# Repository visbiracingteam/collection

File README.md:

# collection
This is my latest git repository.
<br>
author-vishnu bijarniya

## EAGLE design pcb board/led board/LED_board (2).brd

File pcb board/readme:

I have designed boards related to the accumulator of a racing car. These boards need complete knowledge of eagle and PCB design related circuit analysis.
if you want to know about flex pcb and its application, I have done so in finding a solution for a flexible connection that we can add to the thermistor and cell module to connect with pcb board. It may be the solution to the split that we get during running of car.

link: https://drive.google.com/file/d/1qWOxBujmZSA4xRGkHqqwPAvdQpyxN6gt/view?usp=drive_link

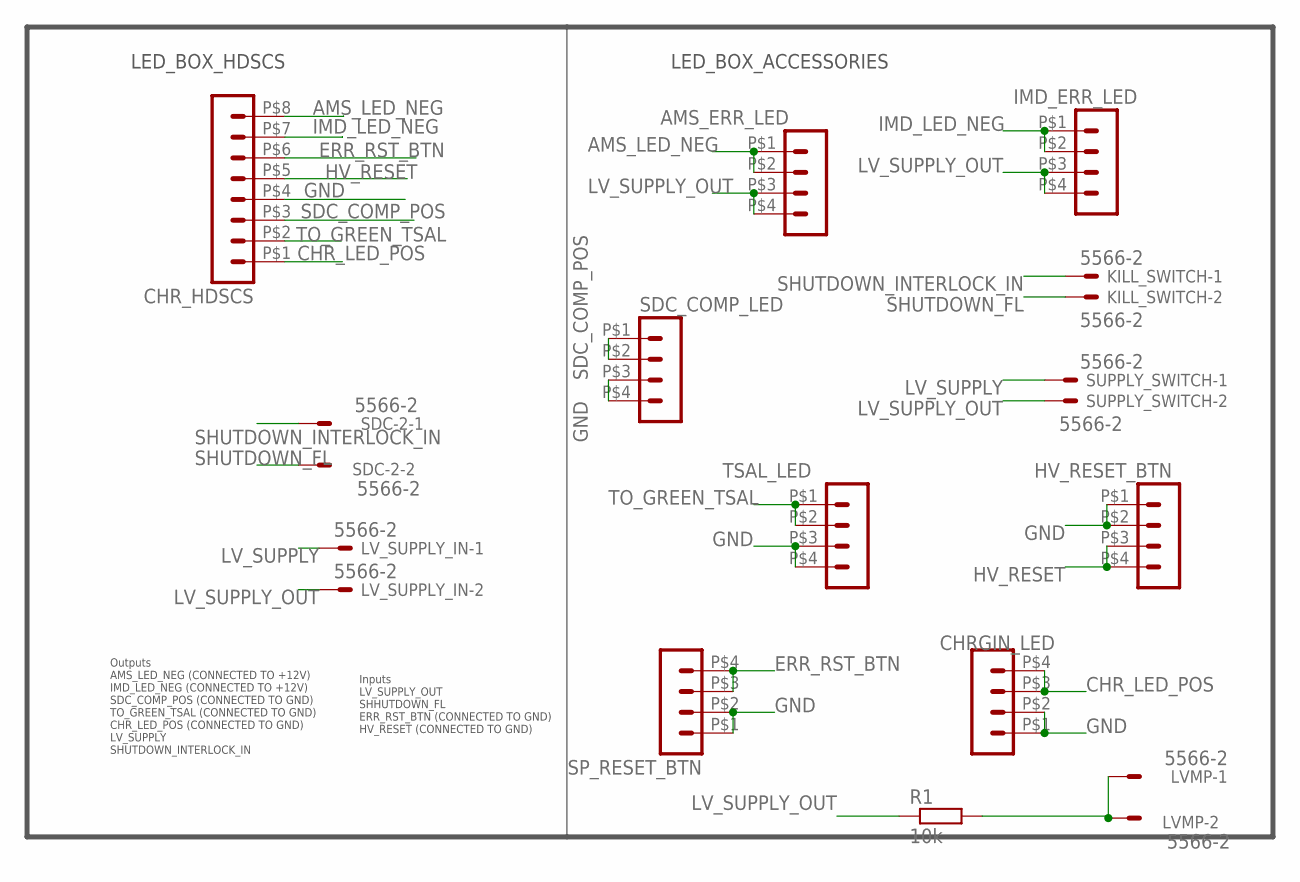
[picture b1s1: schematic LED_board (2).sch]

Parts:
AMS_ERR_LED: HEADER_POS4_43045-0412; 43045-0412
CHRGIN_LED: HEADER_POS4_43045-0412; 43045-0412
CHR_HDSCS: HEADER_POS8_44914-0801; 44914-0801
HV_RESET_BTN: HEADER_POS4_43045-0412; 43045-0412
IMD_ERR_LED: HEADER_POS4_43045-0412; 43045-0412
KILL_SWITCH: 5566-2
LVMP: 5566-2
LV_SUPPLY_IN: 5566-2
R1: 10k; M0805
SDC-2: 5566-2
SDC_COMP_LED: HEADER_POS4_44914-0401; 44914-0401
SP_RESET_BTN: HEADER_POS4_43045-0412; 43045-0412
SUPPLY_SWITCH: 5566-2
TSAL_LED: HEADER_POS4_43045-0412; 43045-0412

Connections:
AMS_LED_NEG: AMS_ERR_LED.P$1 (1), AMS_ERR_LED.P$2 (2), CHR_HDSCS.P$8 (8)
CHR_LED_POS: CHRGIN_LED.P$3 (3), CHRGIN_LED.P$4 (4), CHR_HDSCS.P$1 (1)
ERR_RST_BTN: CHR_HDSCS.P$6 (6), SP_RESET_BTN.P$3 (3), SP_RESET_BTN.P$4 (4)
GND: CHRGIN_LED.P$1 (1), CHRGIN_LED.P$2 (2), CHR_HDSCS.P$4 (4), HV_RESET_BTN.P$1 (1), HV_RESET_BTN.P$2 (2), SDC_COMP_LED.P$3 (3), SDC_COMP_LED.P$4 (4), SP_RESET_BTN.P$1 (1), SP_RESET_BTN.P$2 (2), TSAL_LED.P$3 (3), TSAL_LED.P$4 (4)
HV_RESET: CHR_HDSCS.P$5 (5), HV_RESET_BTN.P$3 (3), HV_RESET_BTN.P$4 (4)
IMD_LED_NEG: CHR_HDSCS.P$7 (7), IMD_ERR_LED.P$1 (1), IMD_ERR_LED.P$2 (2)
LV_SUPPLY: LV_SUPPLY_IN.1, SUPPLY_SWITCH.1
LV_SUPPLY_OUT: AMS_ERR_LED.P$3 (3), AMS_ERR_LED.P$4 (4), IMD_ERR_LED.P$3 (3), IMD_ERR_LED.P$4 (4), LV_SUPPLY_IN.2, R1.1, SUPPLY_SWITCH.2
unnamed: LVMP.1, LVMP.2, R1.2
SDC_COMP_POS: CHR_HDSCS.P$3 (3), SDC_COMP_LED.P$1 (1), SDC_COMP_LED.P$2 (2)
SHUTDOWN_FL: KILL_SWITCH.2, SDC-2.2
SHUTDOWN_INTERLOCK_IN: KILL_SWITCH.1, SDC-2.1
TO_GREEN_TSAL: CHR_HDSCS.P$2 (2), TSAL_LED.P$1 (1), TSAL_LED.P$2 (2)

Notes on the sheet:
Outputs AMS_LED_NEG (CONNECTED TO +12V) IMD_LED_NEG (CONNECTED TO +12V) SDC_COMP_POS (CONNECTED TO GND) TO_GREEN_TSAL (CONNECTED TO GND) CHR_LED_POS (CONNECTED TO GND) LV_SUPPLY SHUTDOWN_INTERLOCK_IN
Inputs LV_SUPPLY_OUT SHHUTDOWN_FL ERR_RST_BTN (CONNECTED TO GND) HV_RESET (CONNECTED TO GND)
LED_BOX_HDSCS
LED_BOX_ACCESSORIES

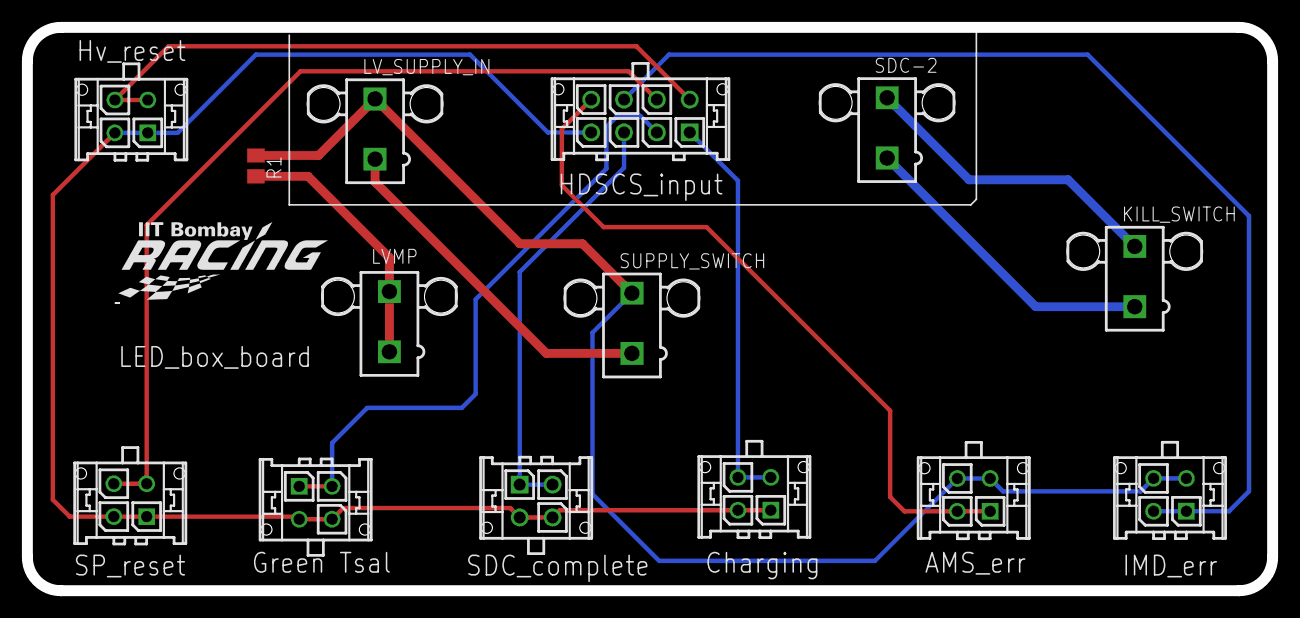
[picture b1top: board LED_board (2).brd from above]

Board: 2 copper layers, 113.7 x 51.4 mm, 15 parts (0 on the bottom side), 13 nets.

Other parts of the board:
U$5: RACING_LOGO_290MIL

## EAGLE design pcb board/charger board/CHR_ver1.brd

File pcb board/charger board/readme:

Here are two charger board versions. Ver2 is updated according to the points noticed after Ver1 completes testing.

The charger board is a safety board that controls the charging of the accumulator by using the IMD and AMS error. 
It is designed to generate a well-shaped analog signal by generating a falling edge and a rising edge signal with a calculated delay.

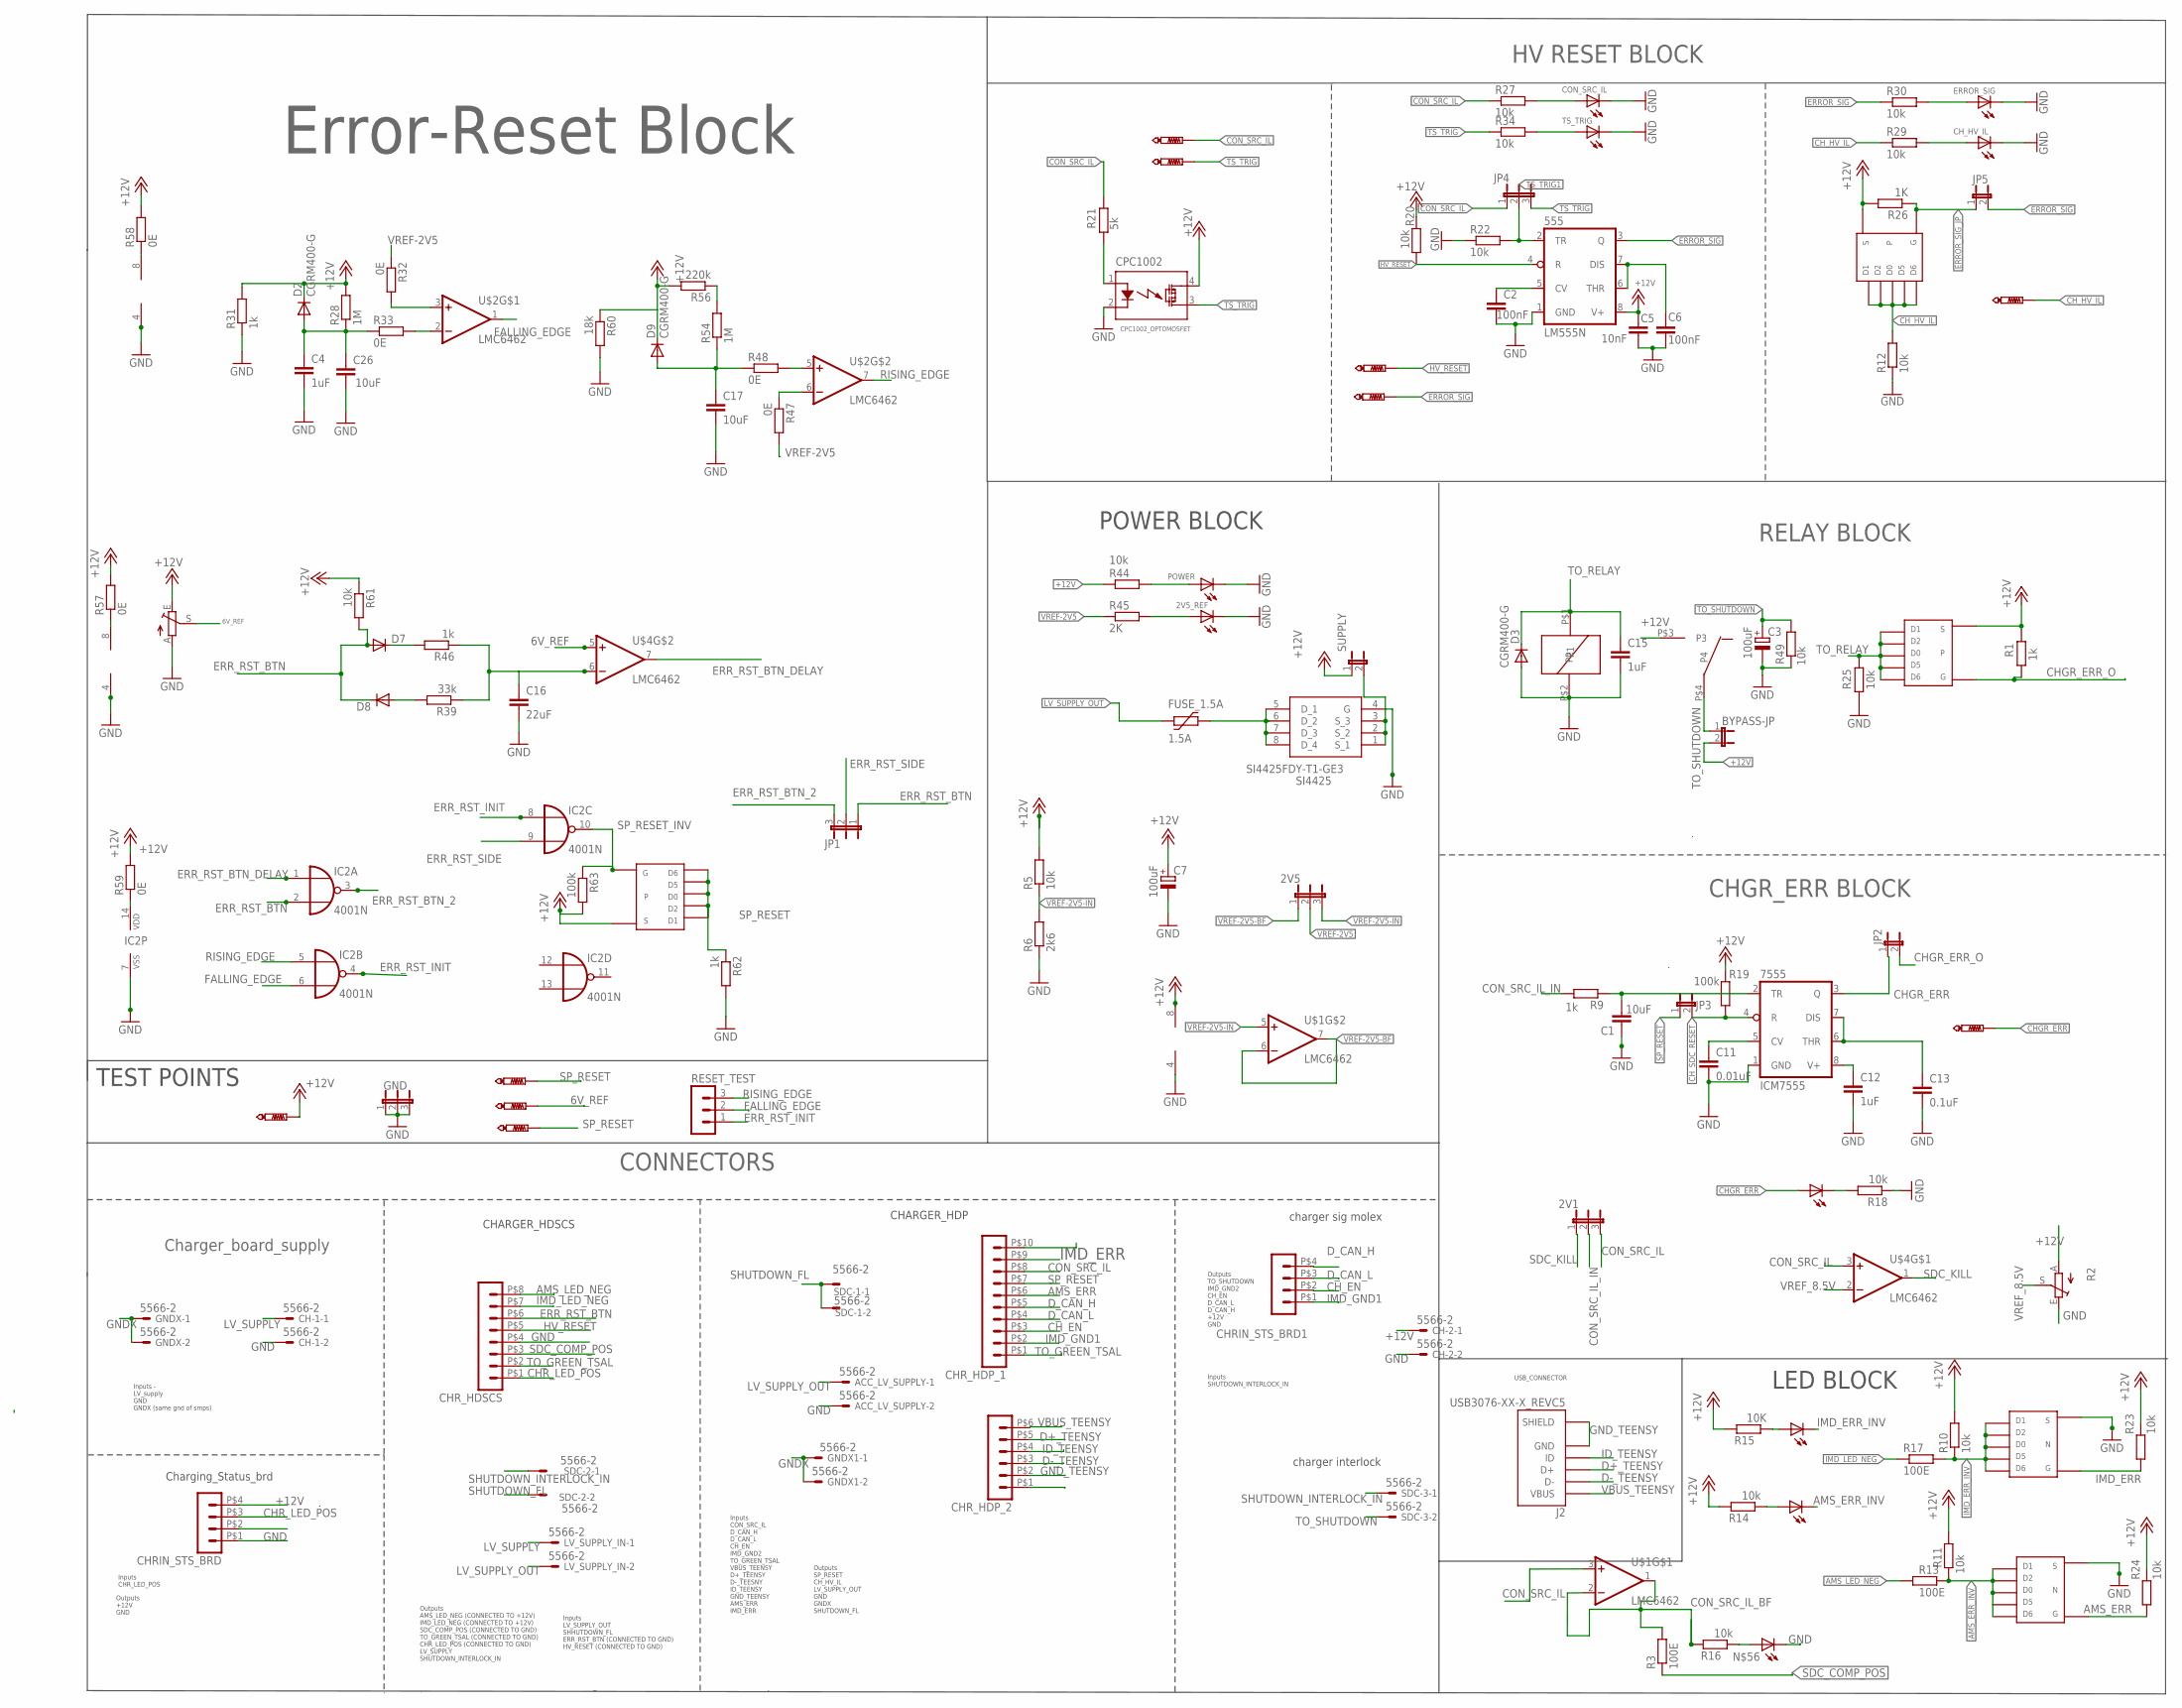
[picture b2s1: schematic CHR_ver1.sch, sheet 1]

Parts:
2V1, 2V5: JP2E; JP2
2V5_REF: LED-FKIT-1206; FKIT-LED-1206
555: LM555N; DIL08
7555: ICM7555; DIL08
+12V: PTR1PAD1-13; P1-13
ACC_LV_SUPPLY: 5566-2
AMS, AMS1: LED-FKIT-1206; FKIT-LED-1206
BYPASS-JP: JP1E; JP1
C1, C17, C26: 10uF; C0805
C2, C6: 100nF; C0805
C3, C7: 100uF; E2,5-6
C4, C12, C15: 1uF; C0805
C5: 10nF; C0805
C11: 0.01uF; C0805
C13: 0.1uF; C0805
C16: 22uF; C0805
CH-1, CH-2: 5566-2
CH-HV-IL: PTR1PAD1-13; P1-13
CHGR-ERR: PTR1PAD1-13; P1-13
CHGR_ERR: LED-FKIT-1206; FKIT-LED-1206
CHRIN_STS_BRD, CHRIN_STS_BRD1: HEADER_POS4_44914-0401; 44914-0401
CHR_HDP_1: HEADER_POS10_44914-1001; 44914-1001
CHR_HDP_2: HEADER_POS6_44914-0601; 44914-0601
CHR_HDSCS: HEADER_POS8_44914-0801; 44914-0801
CH_HV_IL: LED-FKIT-1206; FKIT-LED-1206
CON-SRC-IL: PTR1PAD1-13; P1-13
CON_SRC_IL: LED-FKIT-1206; FKIT-LED-1206
CPC1002: CPC1002_OPTOMOSFET; SOP04
D2, D3, D9: CGRM400-G; SOD-123_MINI-SMA
D7, D8: DIODE-DO214AC; DO214AC
ERROR-SIG: PTR1PAD1-13; P1-13
ERROR_SIG: LED-FKIT-1206; FKIT-LED-1206
FUSE_1.5A: 1.5A; 1206L
GND: JP2E; JP2
GNDX, GNDX1: 5566-2
HV-RESET: PTR1PAD1-13; P1-13
IC2: 4001N; DIL14
IMD: LED-FKIT-1206; FKIT-LED-1206
J2: USB3076-XX-X_REVC5; GCT_USB3076-XX-X_REVC5
JP1, JP4: JP2E; JP2
JP2, JP3, JP5: JP1E; JP1
LV_SUPPLY_IN: 5566-2
POWER: LED-FKIT-1206; FKIT-LED-1206
R1, R9, R31, R46, R62: 1k; R0805
R2: TRIM_EU-S63S; S63S
R3, R13, R17: 100E; M0805
R5, R10, R11, R12, R18, R20, R22, R23, R24, R25, R27, R29, R30, R34, R44, R49, R61: 10k; R0805
R6: 2k6; R0805
R14, R16: 10k; M0805
R15: 10K; M0805
R19, R63: 100k; R0805
R21: 5k; R0805
R26: 1K; R0805
R28, R54: 1M; R0805
R32, R33, R47, R48, R57, R58, R59: 0E; R0805
R39: 33k; R0805
R45: 2K; R0805
R56: 220k; R0805
R60: 18k; R0805
REF_POT1: 10k; S63S
RESET_TEST: MA03-1
SDC-1, SDC-2, SDC-3: 5566-2
SI4425: SI4425FDY-T1-GE3; SOIC127P600X175-8N
SP_RESET, SP_RESET1, SP_RESET2: PTR1PAD1-13; P1-13
SUPPLY: JP1E; JP1
TS-TRIG: PTR1PAD1-13; P1-13
TS_TRIG: LED-FKIT-1206; FKIT-LED-1206
U$1, U$2, U$4: LMC6462; S08
U$3, U$8, U$11: TSOP-6_PMOS
U$5, U$7: TSOP-6_NMOS
U$9: G6DN_RELAY

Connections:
6V_REF: REF_POT1.S, SP_RESET1.TP, U$4.5 (+IN)
+12V: 555.8 (V+), 7555.8 (V+), +12V.TP, BYPASS-JP.2, C5.1, C7.+, C12.1, CH-2.1, CHRIN_STS_BRD.P$4 (4), CPC1002.4, D2.C, D9.C, R1.2, R2.A, R5.2, R10.2, R11.2, R14.2, R15.2, R19.1, R20.2, R23.2, R24.2, R26.2, R28.2, R31.2, R44.1, R56.2, R57.2, R58.2, R59.2, R60.1, R61.1, R63.2, REF_POT1.E, SUPPLY.1, U$1.8 (V+), U$3.S, U$8.S, U$9.P$3 (P3), U$11.S
AMS_ERR: CHR_HDP_1.P$6 (6), R24.1, U$5.G
AMS_ERR_INV: AMS.C, R11.1, R13.2, U$5.1, U$5.2, U$5.5, U$5.6, U$5.D (D0)
AMS_LED_NEG: CHR_HDSCS.P$8 (8), R13.1
CHGR_ERR: 7555.3 (Q), CHGR-ERR.TP, CHGR_ERR.A, JP2.1
CHGR_ERR_O: JP2.2, R1.1, U$3.G
CHR_LED_POS: CHRIN_STS_BRD.P$3 (3), CHR_HDSCS.P$1 (1)
CH_EN: CHRIN_STS_BRD1.P$2 (2), CHR_HDP_1.P$3 (3)
CH_HV_IL: CH-HV-IL.TP, CHR_HDP_1.P$10 (10), R12.2, R29.1, U$8.1, U$8.2, U$8.5, U$8.6, U$8.D (D0)
CH_SDC_RESET: 7555.4 (R), JP3.2, R19.2
CON_SRC_IL: 2V1.3, CHR_HDP_1.P$8 (8), CON-SRC-IL.TP, JP4.1, R21.2, R27.1, U$1.3 (+IN), U$4.3 (+IN)
CON_SRC_IL_BF: R3.2, R16.2, U$1.1 (OUT), U$1.2 (-IN)
CON_SRC_IL_IN: 2V1.2, R9.2
D+_TEENSY: CHR_HDP_2.P$5 (5), J2.3 (D+)
D-_TEENSY: CHR_HDP_2.P$3 (3), J2.2 (D-)
D_CAN_H: CHRIN_STS_BRD1.P$4 (4), CHR_HDP_1.P$5 (5)
D_CAN_L: CHRIN_STS_BRD1.P$3 (3), CHR_HDP_1.P$4 (4)
ERROR_SIG: 555.3 (Q), ERROR-SIG.TP, JP5.2, R30.1
ERROR_SIG_JP: JP5.1, R26.1, U$8.G
ERR_RST_BTN: CHR_HDSCS.P$6 (6), D7.A, D8.C, IC2.2 (I1), JP1.1, R61.2
ERR_RST_BTN_2: IC2.3 (O), JP1.3
ERR_RST_BTN_DELAY: IC2.1 (I0), U$4.7 (OUT)
ERR_RST_INIT: IC2.4 (O), IC2.8 (I0), RESET_TEST.1
ERR_RST_SIDE: IC2.9 (I1), JP1.2
FALLING_EDGE: IC2.6 (I1), RESET_TEST.2, U$2.1 (OUT)
GND: 2V5_REF.C, 555.1 (GND), 7555.1 (GND), ACC_LV_SUPPLY.2, AMS1.C, C1.1, C2.2, C3.-, C4.2, C5.2, C6.2, C7.-, C11.2, C12.2, C13.2, C15.2, C16.2, C17.2, C26.2, CH-1.2, CH-2.2, CHRIN_STS_BRD.P$1 (1), CHR_HDSCS.P$4 (4), CH_HV_IL.C, CON_SRC_IL.C, CPC1002.2, D3.A, ERROR_SIG.C, GND.1, GND.2, GND.3, IC2.7 (VSS), POWER.C, R2.E, R6.1, R12.1, R18.1, R22.1, R25.1, R31.1, R49.1, R60.2, R62.2, REF_POT1.A, SI4425.4 (G), TS_TRIG.C, U$1.4 (V-), U$2.4 (V-), U$4.4 (V-), U$5.S, U$7.S, U$9.P$2 (P2)
GNDX: GNDX.1, GNDX.2, GNDX1.1, GNDX1.2
GND_TEENSY: CHR_HDP_2.P$2 (2), J2.5 (GND), J2.6 (SHIELD), J2.7 (SHIELD), J2.8 (SHIELD), J2.9 (SHIELD), J2.10 (SHIELD), J2.11 (SHIELD)
HV_RESET: 555.4 (R), CHR_HDSCS.P$5 (5), HV-RESET.TP, R20.1
ID_TEENSY: CHR_HDP_2.P$4 (4), J2.4 (ID)
IMD_ERR: CHR_HDP_1.P$9 (9), R23.1, U$7.G
IMD_ERR_INV: IMD.C, R10.1, R17.2, U$7.1, U$7.2, U$7.5, U$7.6, U$7.D (D0)
IMD_GND1: CHRIN_STS_BRD1.P$1 (1), CHR_HDP_1.P$2 (2)
IMD_LED_NEG: CHR_HDSCS.P$7 (7), R17.1
LV_SUPPLY: CH-1.1, LV_SUPPLY_IN.1
LV_SUPPLY_OUT: ACC_LV_SUPPLY.1, FUSE_1.5A.P$1 (1), LV_SUPPLY_IN.2
unnamed: 7555.2 (TR), C1.2, R9.1
unnamed: 555.5 (CV), C2.1
unnamed: CHGR_ERR.C, R18.2
unnamed: 555.6 (THR), 555.7 (DIS), C6.1
unnamed: CPC1002.1, R21.1
unnamed: CON_SRC_IL.A, R27.2
unnamed: CH_HV_IL.A, R29.2
unnamed: ERROR_SIG.A, R30.2
unnamed: R34.2, TS_TRIG.A
unnamed: 7555.5 (CV), C11.1
unnamed: 7555.6 (THR), 7555.7 (DIS), C13.1
unnamed: SI4425.1 (S_1), SI4425.2 (S_2), SI4425.3 (S_3), SUPPLY.2
unnamed: FUSE_1.5A.P$2 (2), SI4425.5 (D_1), SI4425.6 (D_2), SI4425.7 (D_3), SI4425.8 (D_4)
unnamed: POWER.A, R44.2
unnamed: 2V5_REF.A, R45.2
unnamed: AMS.A, R14.1
unnamed: IMD.A, R15.1
unnamed: C4.1, C26.1, D2.A, R28.1, R33.1
unnamed: R32.2, U$2.3 (+IN)
unnamed: R33.2, U$2.2 (-IN)
unnamed: D8.A, R39.2
unnamed: D7.C, R46.2
unnamed: C16.1, R39.1, R46.1, U$4.6 (-IN)
unnamed: R47.1, U$2.6 (-IN)
unnamed: C17.1, D9.A, R48.1, R54.1
unnamed: R48.2, U$2.5 (+IN)
unnamed: R54.2, R56.1
unnamed: R58.1, U$2.8 (V+)
unnamed: R57.1, U$4.8 (V+)
unnamed: IC2.14 (VDD), R59.1
unnamed: AMS1.A, R16.1
RISING_EDGE: IC2.5 (I0), RESET_TEST.3, U$2.7 (OUT)
SDC_COMP_POS: CHR_HDSCS.P$3 (3), R3.1
SDC_KILL: 2V1.1, U$4.1 (OUT)
SHUTDOWN_FL: SDC-1.1, SDC-1.2, SDC-2.2
SHUTDOWN_INTERLOCK_IN: SDC-2.1, SDC-3.1
SP_RESET: CHR_HDP_1.P$7 (7), JP3.1, R62.1, SP_RESET.TP, SP_RESET2.TP, U$11.1, U$11.2, U$11.5, U$11.6, U$11.D (D0)
SP_RESET_INV: IC2.10 (O), R63.1, U$11.G
TO_GREEN_TSAL: CHR_HDP_1.P$1 (1), CHR_HDSCS.P$2 (2)
TO_RELAY: C15.1, D3.C, R25.2, U$3.1, U$3.2, U$3.5, U$3.6, U$3.D (D0), U$9.P$1 (P1)
TO_SHUTDOWN: BYPASS-JP.1, C3.+, R49.2, SDC-3.2, U$9.P$4 (P4)
TS_TRIG: CPC1002.3, JP4.3, R34.1, TS-TRIG.TP
TS_TRIG1: 555.2 (TR), JP4.2, R22.2
VBUS_TEENSY: CHR_HDP_2.P$6 (6), J2.1 (VBUS)
VREF-2V5: 2V5.2, R32.1, R45.1, R47.2
VREF-2V5-BF: 2V5.1, U$1.6 (-IN), U$1.7 (OUT)
VREF-2V5-IN: 2V5.3, R5.1, R6.2, U$1.5 (+IN)
VREF_8.5V: R2.S, U$4.2 (-IN)

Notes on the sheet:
CHGR_ERR BLOCK
RELAY BLOCK
CONNECTORS
POWER BLOCK
TEST POINTS
LED BLOCK
HV RESET BLOCK
Charger_board_supply
charger sig molex
CHARGER_HDSCS
CHARGER_HDP
Charging_Status_brd
charger interlock
Error-Reset Block
Inputs - LV_supply GND GNDX (same gnd of smps)
Inputs CHR_LED_POS
Outputs +12V GND
Outputs AMS_LED_NEG (CONNECTED TO +12V) IMD_LED_NEG (CONNECTED TO +12V) SDC_COMP_POS (CONNECTED TO GND) TO_GREEN_TSAL (CONNECTED TO GND) CHR_LED_POS (CONNECTED TO GND) LV_SUPPLY SHUTDOWN_INTERLOCK_IN
Inputs LV_SUPPLY_OUT SHHUTDOWN_FL ERR_RST_BTN (CONNECTED TO GND) HV_RESET (CONNECTED TO GND)
Inputs CON_SRC_IL D_CAN_H D_CAN_L CH_EN IMD_GND2 TO_GREEN_TSAL VBUS_TEENSY D+_TEENSY D-_TEESNY ID_TEENSY GND_TEENSY AMS_ERR IMD_ERR
Outputs SP_RESET CH_HV_IL LV_SUPPLY_OUT GND GNDX SHUTDOWN_FL
Inputs SHUTDOWN_INTERLOCK_IN
Outputs TO_SHUTDOWN IMD_GND2 CH_EN D_CAN_L D_CAN_H +12V GND
USB_CONNECTOR

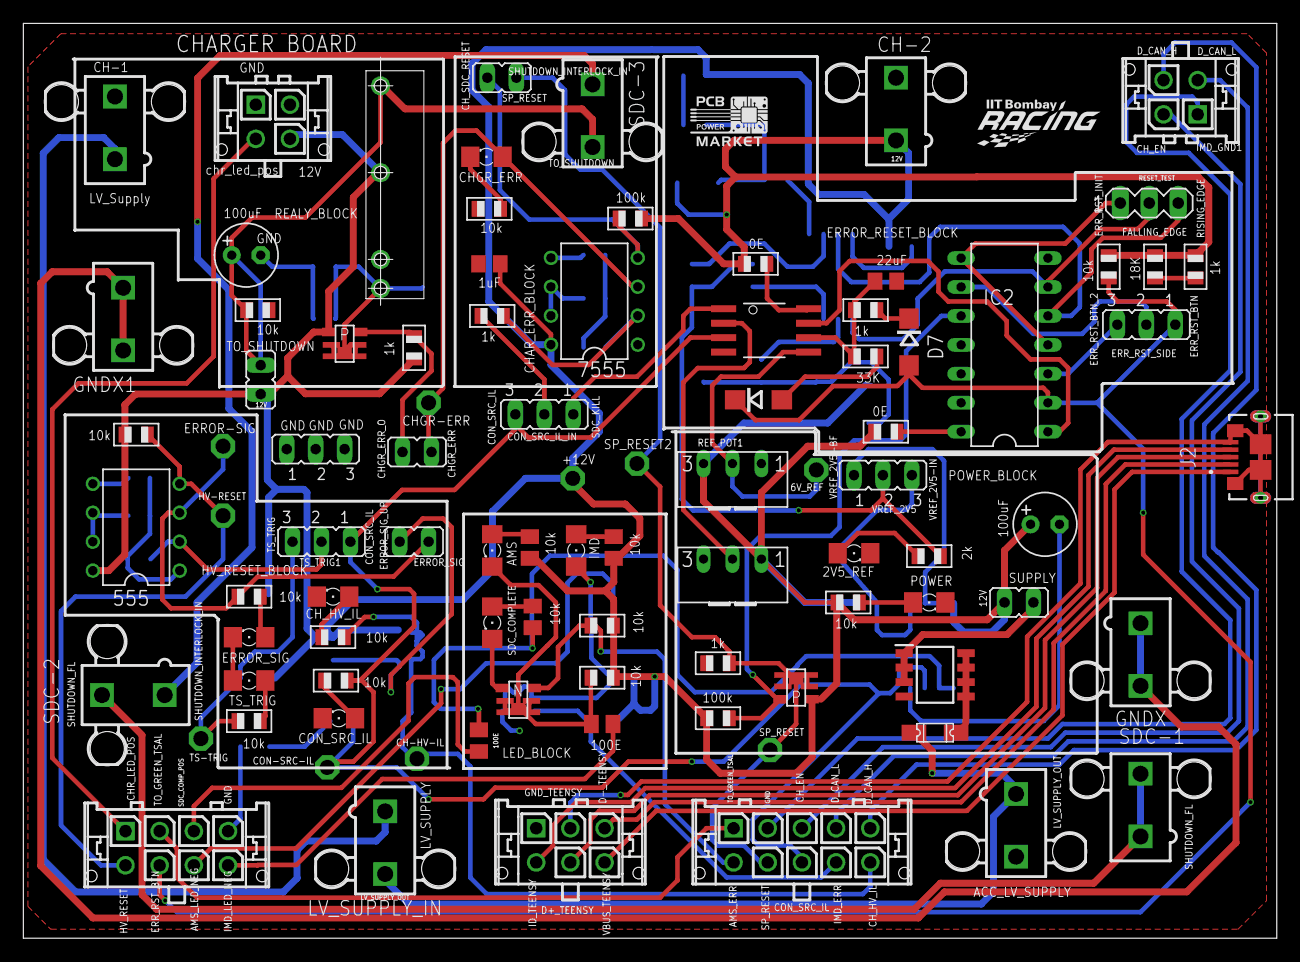
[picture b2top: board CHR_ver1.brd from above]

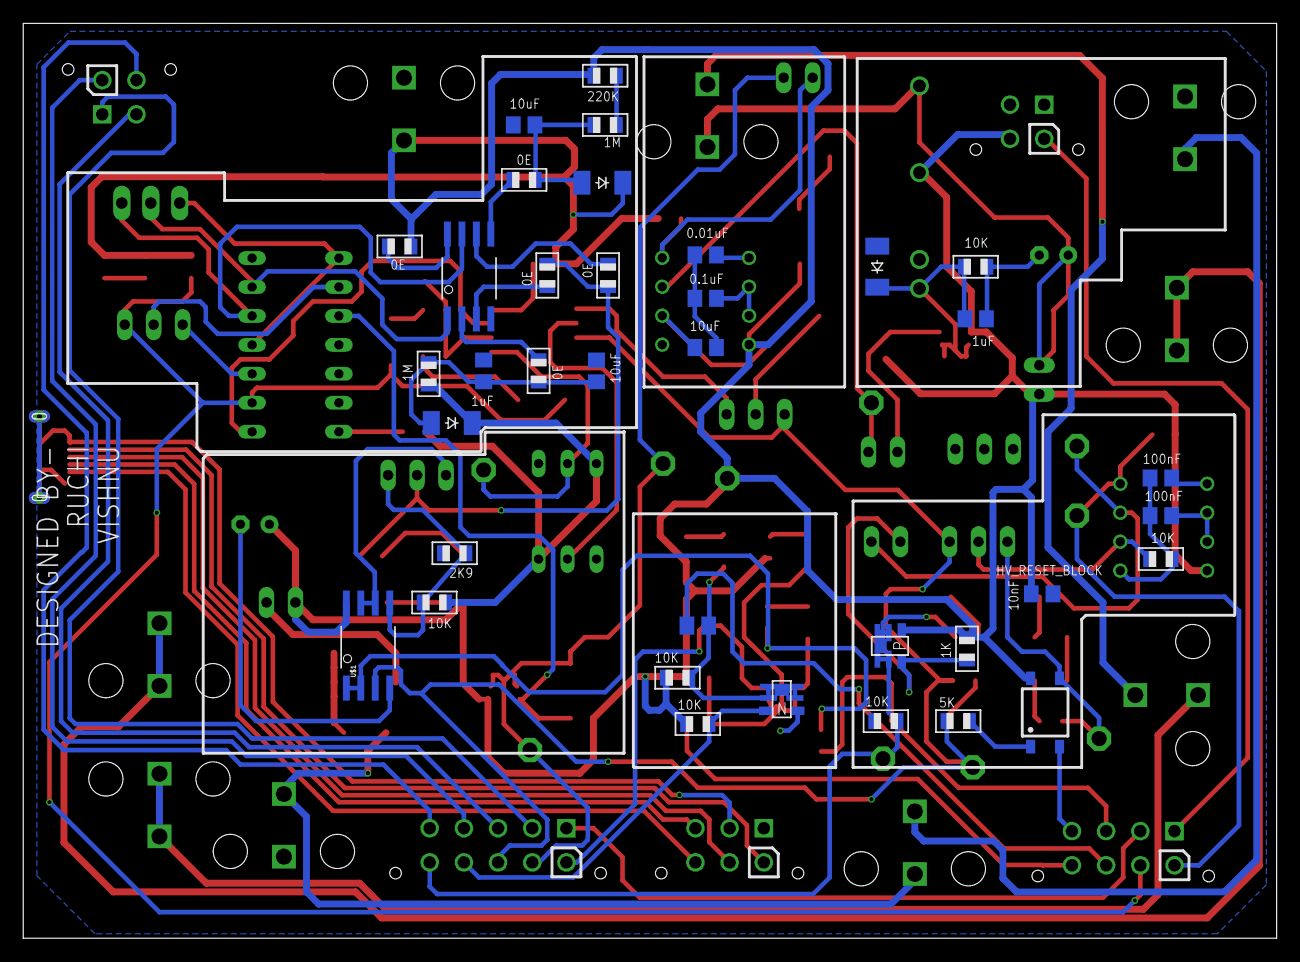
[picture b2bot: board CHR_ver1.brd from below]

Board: 2 copper layers, 110.0 x 80.3 mm, 130 parts (36 on the bottom side), 85 nets.

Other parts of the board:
U$13: LOGO_PCBPOWER; 270X170
U$15: IITBR_LOGO

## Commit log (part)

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2025-05-16 add next line
2025-05-16 Create placeholder
2025-05-16 Create Digital Logic Design
2025-07-11 Create Discrete Audio Amplifier with Smart Power Protection
